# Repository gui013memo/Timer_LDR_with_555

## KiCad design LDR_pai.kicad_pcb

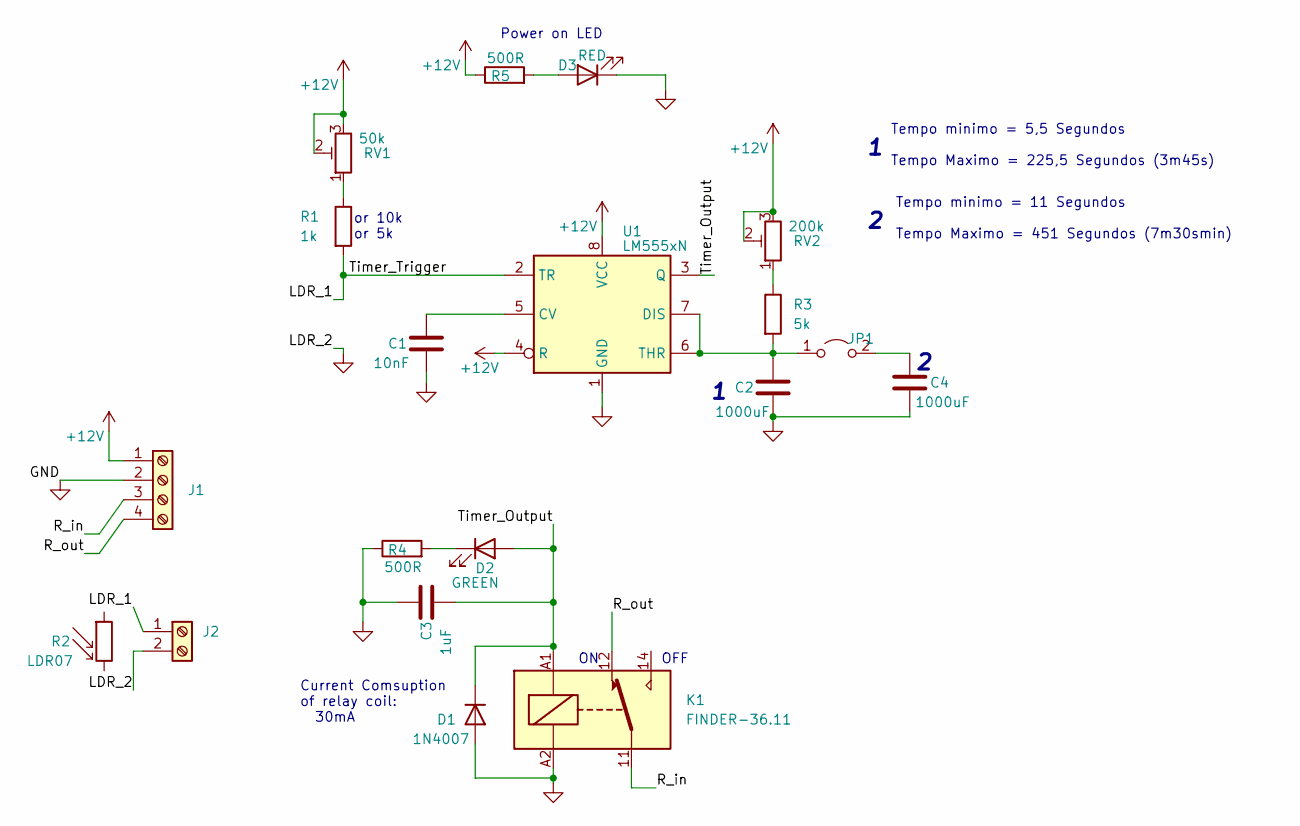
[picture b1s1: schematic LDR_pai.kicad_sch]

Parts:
C1: 10nF; C_Radial_D5.0mm_H5.0mm_P2.00mm
C2, C4: 1000uF; C_Radial_D8.0mm_H7.0mm_P3.50mm
C3: 1uF; C_Radial_D5.0mm_H5.0mm_P2.00mm
D1: 1N4007; D_5W_P12.70mm_Horizontal
D2: GREEN; LED_D5.0mm_FlatTop
D3: RED; LED_D5.0mm_FlatTop
J1: Screw_Terminal_01x04; TerminalBlock_Phoenix_MKDS-1,5-4-5.08_1x04_P5.08mm_Horizont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
J2: Screw_Terminal_01x02; TerminalBlock_Phoenix_MKDS-1,5-2-5.08_1x02_P5.08mm_Horizont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
JP1: Jumper_2_Open; TestPoint_2Pads_Pitch2.54mm_Drill0.8mm
K1: FINDER-36.11; Relay_SPDT_Finder_36.11
R1: 1k; R_Axial_DIN0207_L6.3mm_D2.5mm_P10.16mm_Horizontal
R2: LDR07; R_LDR_5.1x4.3mm_P3.4mm_Vertical
R3: 5k; R_Axial_DIN0207_L6.3mm_D2.5mm_P10.16mm_Horizontal
R4, R5: 500R; R_Axial_DIN0207_L6.3mm_D2.5mm_P10.16mm_Horizontal
RV1: 50k; Potentiometer_Alps_RK163_Single_Horizontal
RV2: 200k; Potentiometer_Alps_RK163_Single_Horizontal
U1: LM555xN; DIP-8_W7.62mm

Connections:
+12V: J1.1, R5.1, RV1.2, RV1.3, RV2.2, RV2.3, U1.4 (R), U1.8 (VCC)
/LDR_1: J2.1, R1.2, U1.2 (TR)
/R_in: J1.3, K1.11
/R_out: J1.4, K1.12
/Timer_Output: C3.2, D1.1 (K), D2.2 (A), K1.A1, U1.3 (Q)
GND: C1.2, C2.2, C3.1, C4.2, D1.2 (A), D3.1 (K), J1.2, J2.2, K1.A2, R4.1, U1.1 (GND)
unnamed: C1.1, U1.5 (CV)
unnamed: C2.1, JP1.1 (A), R3.2, U1.6 (THR), U1.7 (DIS)
unnamed: C4.1, JP1.2 (B)
unnamed: D2.1 (K), R4.2
unnamed: D3.2 (A), R5.2
unnamed: R1.1, RV1.1
unnamed: R3.1, RV2.1

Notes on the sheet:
Power on LED
Tempo minimo = 5,5 Segundos Tempo Maximo = 225,5 Segundos (3m45s)
Tempo minimo = 11 Segundos Tempo Maximo = 451 Segundos (7m30smin)
OFF
Current Comsuption of relay coil: 30mA
or 10k or 5k

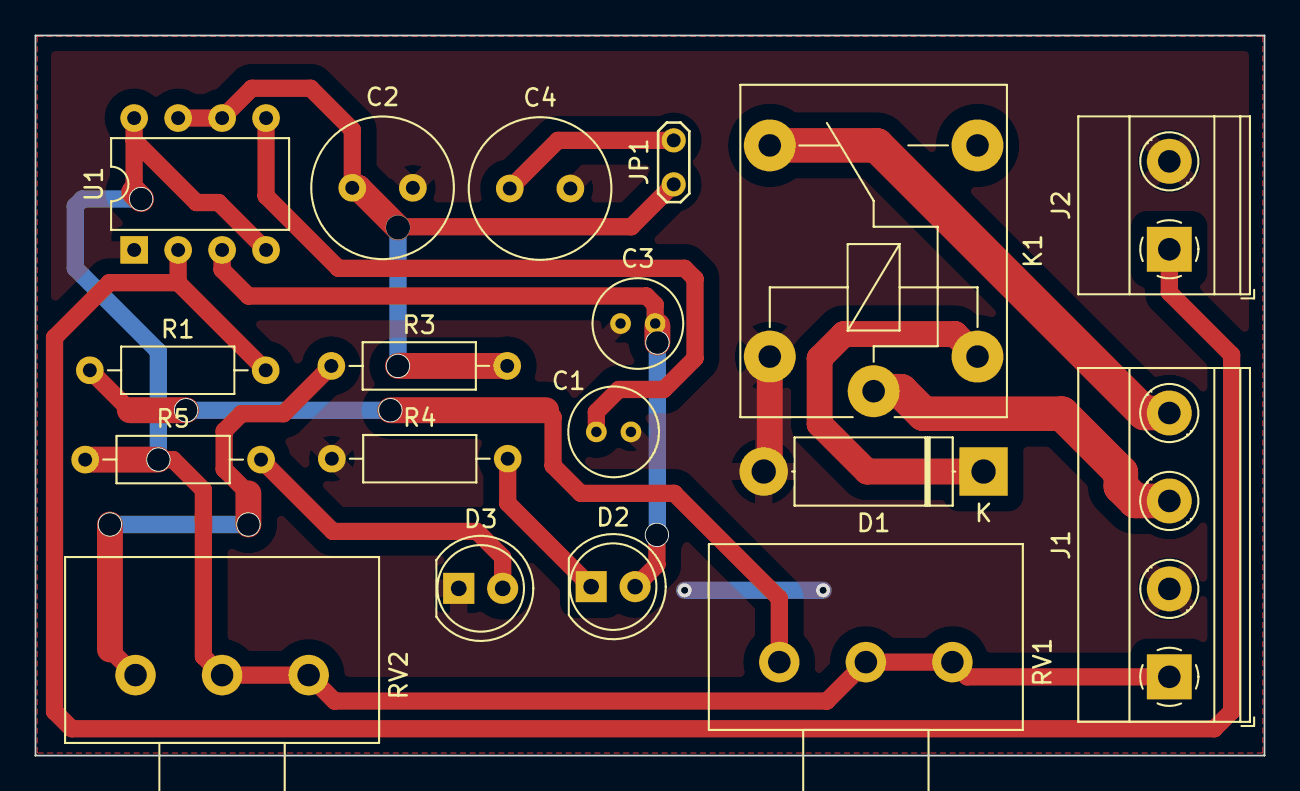
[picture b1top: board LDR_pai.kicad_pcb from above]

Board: 2 copper layers, 71.0 x 41.6 mm, 18 parts (0 on the bottom side), 13 nets.

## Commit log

2022-08-30 projeto finalizado
2022-10-07 data refresh
